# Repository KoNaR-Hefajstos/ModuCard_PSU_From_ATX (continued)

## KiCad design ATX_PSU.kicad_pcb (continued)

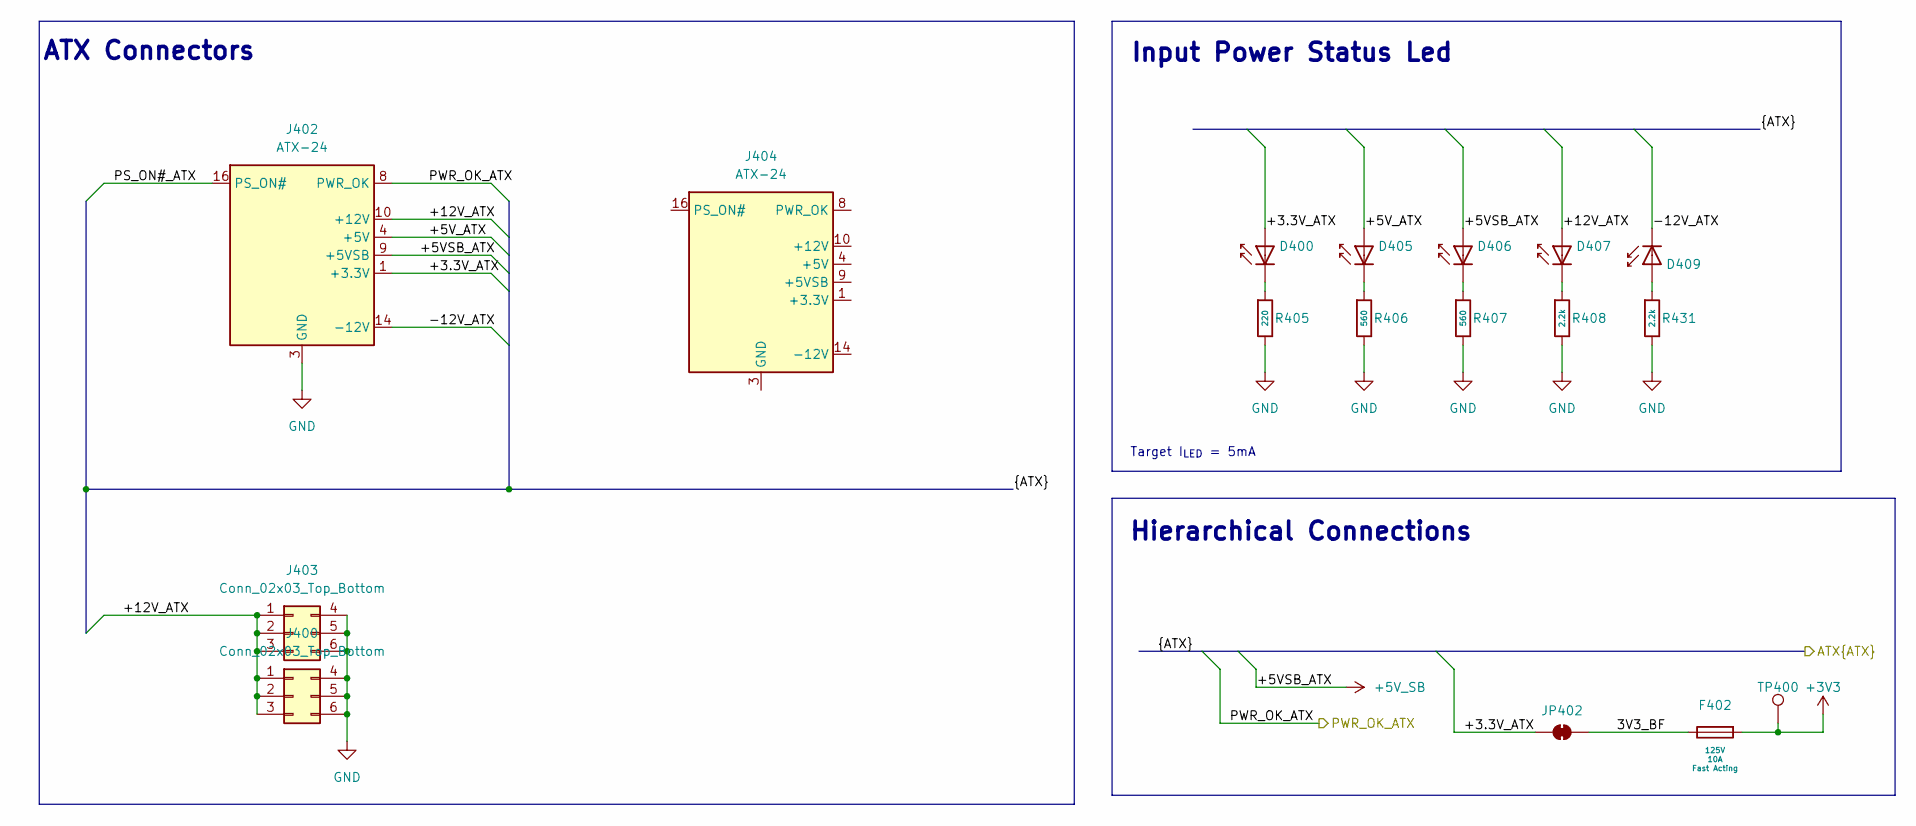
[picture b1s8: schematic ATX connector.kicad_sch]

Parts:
D400, D405, D406, D407, D409: Green; D_0603; Part 19-217/GHC-YR1S2/6T; LCSC C2986059
F402: 10A; Fuse_2410_6125; Voltage Rating 125V; LCSC C136374
J400, J403: Conn_02x03_Top_Bottom; Molex_Mini-Fit_Jr_5569-06A2_2x03_P4.20mm_Horizontal
J402: ATX-24; Molex_Mini-Fit_Jr_5566-24A_2x12_P4.20mm_Vertical
J404: ATX-24; Molex_Mini-Fit_Jr_5569-24A2_2x12_P4.20mm_Horizontal
JP402: Test Buck Vout; SolderJumper-2_P1.3mm_Bridged_RoundedPad1.0x1.5mm
R405: 220; R_0402; Overload Voltage (Max) 50V; Tolerance ±1%; Part 0402WGF1002TCE; LCSC C25744
R406, R407: 560; R_0402; Overload Voltage (Max) 50V; Tolerance ±1%; Part 0402WGF1002TCE; LCSC C25744
R408, R431: 2.2k; R_0402; Overload Voltage (Max) 50V; Tolerance ±1%; Part 0402WGF1002TCE; LCSC C25744
TP400: TestPoint; TestPoint_Pad_D1.0mm

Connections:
+3V3: F402.1, TP400.1; also elsewhere on the board
+5V_SB: D406.2, J402.9 (+5VSB); also elsewhere on the board
/ATX connector/3V3_BF: F402.2, JP402.2 (B)
/ATX connector/+3.3V_ATX: D400.2, J402.1 (+3.3V), J402.2 (+3.3V), J402.12 (+3.3V), J402.13 (+3.3V), JP402.1 (A); also elsewhere on the board
/ATX connector/+5V_ATX: D405.2, J402.4 (+5V), J402.6 (+5V), J402.21 (+5V), J402.22 (+5V), J402.23 (+5V); also elsewhere on the board
/ATX connector/+12V_ATX: D407.2, J400.1, J400.2, J400.3, J402.10 (+12V), J402.11 (+12V), J403.1, J403.2, J403.3; also elsewhere on the board
/ATX connector/-12V_ATX: D409.1, J402.14 (-12V)
/ATX connector/PS_ON#_ATX: J402.16 (PS_ON#); also elsewhere on the board
/ATX connector/PWR_OK_ATX: J402.8 (PWR_OK); also elsewhere on the board
GND: J400.4, J400.5, J400.6, J402.3 (GND), J402.5 (GND), J402.7 (GND), J402.15 (GND), J402.17 (GND), J402.18 (GND), J402.19 (GND), J402.24 (GND), J403.4, J403.5, J403.6, R405.2, R406.2, R407.2, R408.2, R431.2; also elsewhere on the board
unnamed: D400.1, R405.1
unnamed: D405.1, R406.1
unnamed: D406.1, R407.1
unnamed: D407.1, R408.1
unnamed: D409.2, R431.1
unnamed: J404.1 (+3.3V), J404.2 (+3.3V), J404.12 (+3.3V), J404.13 (+3.3V)
unnamed: J404.10 (+12V), J404.11 (+12V)
unnamed: J404.3 (GND), J404.5 (GND), J404.7 (GND), J404.15 (GND), J404.17 (GND), J404.18 (GND), J404.19 (GND), J404.24 (GND)
unnamed: J404.4 (+5V), J404.6 (+5V), J404.21 (+5V), J404.22 (+5V), J404.23 (+5V)

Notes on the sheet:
ATX Connectors
Hierarchical Connections
Target I_{LED} = 5mA
Input Power Status Led

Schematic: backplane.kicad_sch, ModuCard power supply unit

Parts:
J200: 09031967921; DIN41612_R_3x32_Female_Horizontal_THT; PARTREV D
TP401, TP402: TestPoint; TestPoint_Pad_D1.0mm
U402: TPD2E2U06DCK; SOT-323_SC-70; LCSC C5350871

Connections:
+5V: J200.a3, J200.b3, J200.c3; also elsewhere on the board
+5V_SB: TP401.1; also elsewhere on the board
+12V: J200.a11, J200.a12, J200.a27, J200.a28, J200.a29, J200.a30, J200.a31, J200.b11, J200.b12, J200.c11, J200.c12; also elsewhere on the board
+24V: J200.a14, J200.a16, J200.a17, J200.b14, J200.c14; also elsewhere on the board
/Backplane/BACKPLANE.D+: J200.a2, U402.2; also elsewhere on the board
/Backplane/BACKPLANE.D-: J200.c2, U402.1; also elsewhere on the board
/Backplane/CAN1.+: J200.a5, J200.b5, J200.c5; also elsewhere on the board
/Backplane/CAN1.-: J200.a6, J200.b6, J200.c6; also elsewhere on the board
/Backplane/CAN2.+: J200.a8, J200.b8, J200.c8; also elsewhere on the board
/Backplane/CAN2.-: J200.a9, J200.b9, J200.c9; also elsewhere on the board
/Backplane/GPIOC0: J200.b16
/Backplane/GPIOC1: J200.b17
/Backplane/GPIOC2: J200.b18
/Backplane/GPIOC3: J200.b19
/Backplane/GPIOC4: J200.b20
/Backplane/GPIOC5: J200.b21
/Backplane/GPIOC6: J200.b22
/Backplane/GPIOC7: J200.b23
/Backplane/GPIOC8: J200.b24
/Backplane/GPIOC9: J200.b25
/Backplane/GPIOC10: J200.b26
/Backplane/GPIOC11: J200.b27
/Backplane/GPIOC12: J200.b28
/Backplane/GPIOC13: J200.b29
/Backplane/GPIOC14: J200.b30
/Backplane/GPIOC15: J200.b31
/Backplane/GPIOR0: J200.c16
/Backplane/GPIOR1: J200.c17
/Backplane/GPIOR2: J200.c18
/Backplane/GPIOR3: J200.c19
/Backplane/GPIOR4: J200.c20
/Backplane/GPIOR5: J200.c21
/Backplane/GPIOR6: J200.c22
/Backplane/GPIOR7: J200.c23
/Backplane/GPIOR8: J200.c24
/Backplane/GPIOR9: J200.c25
/Backplane/GPIOR10: J200.c26
/Backplane/GPIOR11: J200.c27
/Backplane/GPIOR12: J200.c28
/Backplane/GPIOR13: J200.c29
/Backplane/GPIOR14: J200.c30
/Backplane/GPIOR15: J200.c31
GND: J200.a1, J200.a4, J200.a7, J200.a10, J200.a13, J200.a15, J200.a18, J200.a19, J200.a20, J200.a21, J200.a22, J200.a23, J200.a24, J200.a25, J200.a26, J200.a32, J200.b1, J200.b2, J200.b4, J200.b7, J200.b10, J200.b13, J200.b15, J200.b32, J200.c1, J200.c4, J200.c7, J200.c10, J200.c13, J200.c15, J200.c32, TP402.1, U402.3; also elsewhere on the board

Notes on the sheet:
USB
CAN
SPECIAL ADDITIONAL CONNECTIONS
POWER FLAGS
USB

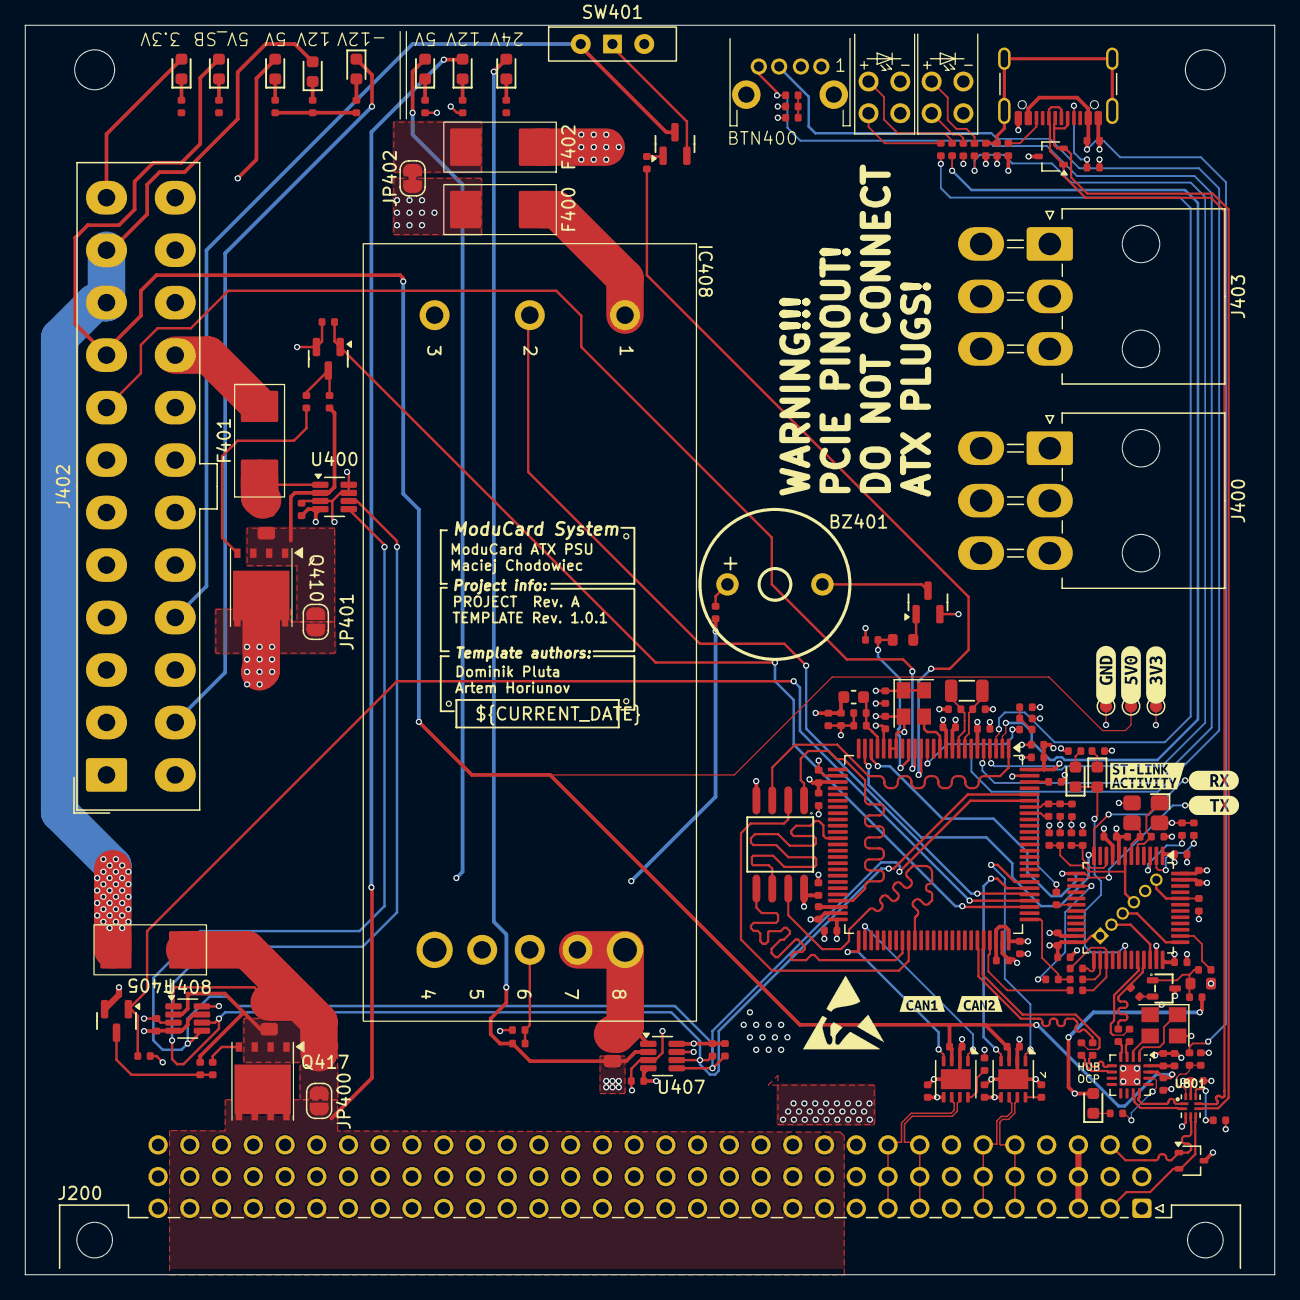
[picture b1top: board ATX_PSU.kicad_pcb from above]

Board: 4 copper layers, 100.0 x 100.0 mm, 177 parts (1 on the bottom side), 127 nets.

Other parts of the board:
kibuzzard-67B20BD5: G***; kibuzzard-67B20BD5
kibuzzard-67B219C6: G***; kibuzzard-67B219C6
kibuzzard-67B643DE: G***; kibuzzard-67B643DE
kibuzzard-67B643EE: G***; kibuzzard-67B643EE
kibuzzard-67B2198C: G***; kibuzzard-67B2198C
kibuzzard-67B37005: G***; kibuzzard-67B37005
kibuzzard-67B37472: G***; kibuzzard-67B37472
kibuzzard-67E7D86B: G***; kibuzzard-67E7D86B

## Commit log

2026-01-11 updated excluded parts
2026-04-18 layout rework
    mostly done, PCBA to do
2026-04-18 add 2x6pin PCIe molex + PCBA to check
    should work now
2026-04-20 generated final gerber
